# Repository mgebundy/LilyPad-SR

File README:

This work is licensed under the Creative Commons Attribution-ShareAlike 3.0 Unported License. To view a copy of this license, visit http://creativecommons.org/licenses/by-sa/3.0/ or send a letter to Creative Commons, 444 Castro Street, Suite 900, Mountain View, California, 94041, USA.

Based on LilyPad for Arduino by Leah Buechley

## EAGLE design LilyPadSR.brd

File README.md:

This work is licensed under the Creative Commons Attribution-ShareAlike 3.0 Unported License. To view a copy of this license, visit http://creativecommons.org/licenses/by-sa/3.0/ or send a letter to Creative Commons, 444 Castro Street, Suite 900, Mountain View, California, 94041, USA.

Based on LilyPad for Arduino by [Leah Buechley](http://web.media.mit.edu/~leah/LilyPad/)
Using elements from the [SparkFun Eagle Library](http://github.com/sparkfun/SparkFun-Eagle-Library)

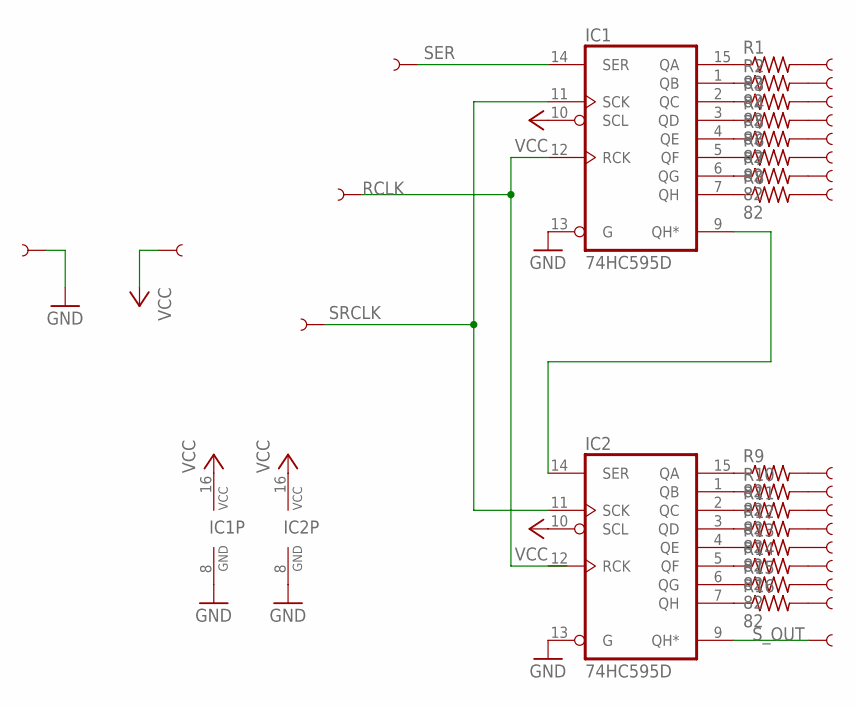
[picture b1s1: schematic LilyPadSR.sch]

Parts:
IC1, IC2: 74HC595D; SO16
R1, R2, R3, R4, R5, R6, R7, R8, R9, R10, R11, R12, R13, R14, R15, R16: 82; R0201
U$1, U$2, U$3, U$4, U$5, U$6, U$7, U$8, U$9, U$10, U$11, U$12, U$13, U$14, U$15, U$16, U$17, U$18, U$19, U$20, U$21, U$22: SEWTAP1; PETAL-LONG-1

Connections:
GND: IC1.8 (GND), IC1.13 (G), IC2.8 (GND), IC2.13 (G), U$22.1
unnamed: IC1.15 (QA), R1.1
unnamed: IC1.1 (QB), R2.1
unnamed: IC1.2 (QC), R3.1
unnamed: IC1.3 (QD), R4.1
unnamed: IC1.4 (QE), R5.1
unnamed: IC1.5 (QF), R6.1
unnamed: IC1.6 (QG), R7.1
unnamed: IC1.7 (QH), R8.1
unnamed: IC2.15 (QA), R9.1
unnamed: IC2.1 (QB), R10.1
unnamed: IC2.2 (QC), R11.1
unnamed: IC2.3 (QD), R12.1
unnamed: IC2.4 (QE), R13.1
unnamed: IC2.5 (QF), R14.1
unnamed: IC2.6 (QG), R15.1
unnamed: IC2.7 (QH), R16.1
unnamed: IC1.9 (QH*), IC2.14 (SER)
Q1: R1.2, U$2.1
Q2: R2.2, U$3.1
Q3: R3.2, U$4.1
Q4: R4.2, U$5.1
Q5: R5.2, U$6.1
Q6: R6.2, U$7.1
Q7: R7.2, U$8.1
Q8: R8.2, U$9.1
Q9: R9.2, U$10.1
Q10: R10.2, U$11.1
Q11: R11.2, U$12.1
Q12: R12.2, U$13.1
Q13: R13.2, U$14.1
Q14: R14.2, U$15.1
Q15: R15.2, U$16.1
Q16: R16.2, U$17.1
RCLK: IC1.12 (RCK), U$19.1
SER: IC1.14 (SER), U$18.1
SRCLK: IC2.11 (SCK), U$20.1
S_OUT: IC2.9 (QH*), U$1.1
VCC: IC1.10 (SCL), IC1.16 (VCC), IC2.10 (SCL), IC2.16 (VCC), U$21.1

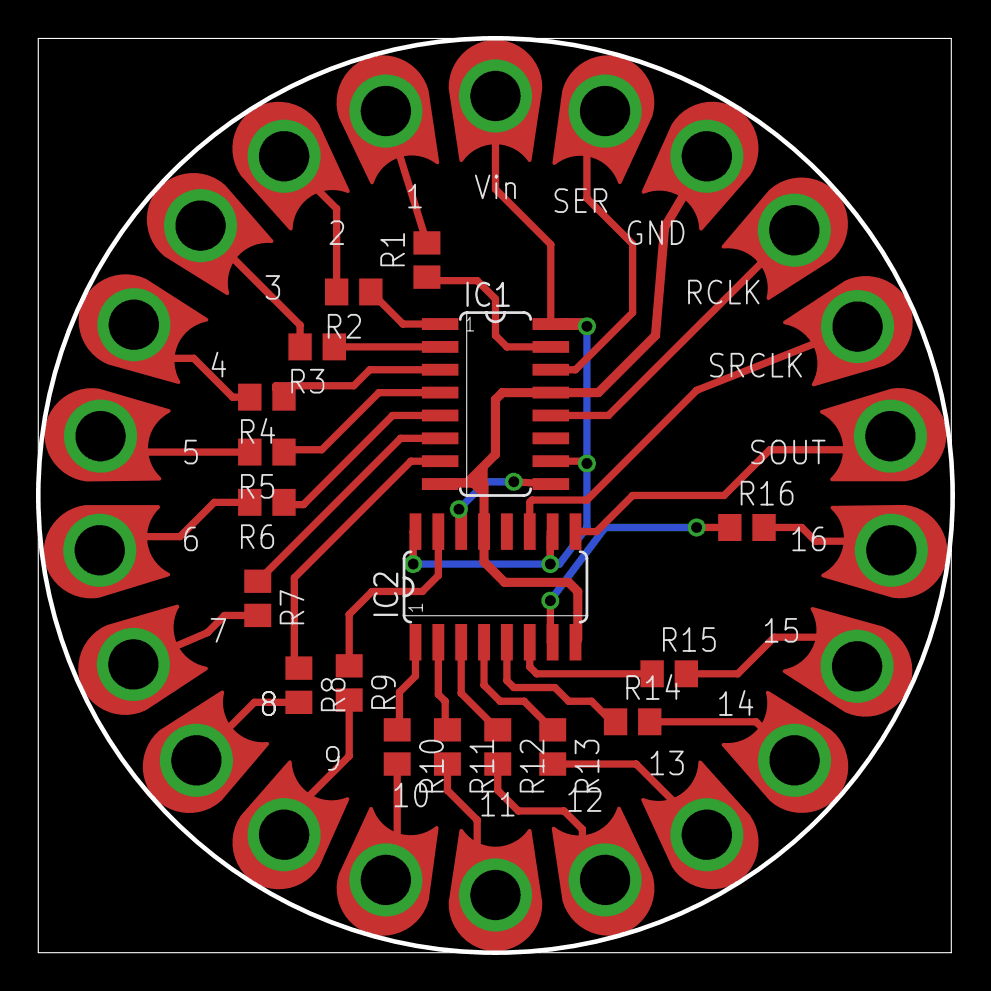
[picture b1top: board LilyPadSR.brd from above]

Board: 2 copper layers, 50.8 x 50.8 mm, 40 parts (0 on the bottom side), 39 nets.

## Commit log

2012-01-10 angle of resistors. started aligning sewtaps
2012-01-10 readme update
2012-01-11 alignment and routing
2012-01-12 removed right angles
2012-01-15 labelling
2012-01-16 generate gerber files
2012-01-17 new gerber files
2012-01-24 design fixes and new job processed for batchpcb
2012-01-24 minor fix
2012-03-29 switched 0201 resistors for 0805. removed gerber files, new ones to be generated
2012-04-09 new design outputted and gerber generated
